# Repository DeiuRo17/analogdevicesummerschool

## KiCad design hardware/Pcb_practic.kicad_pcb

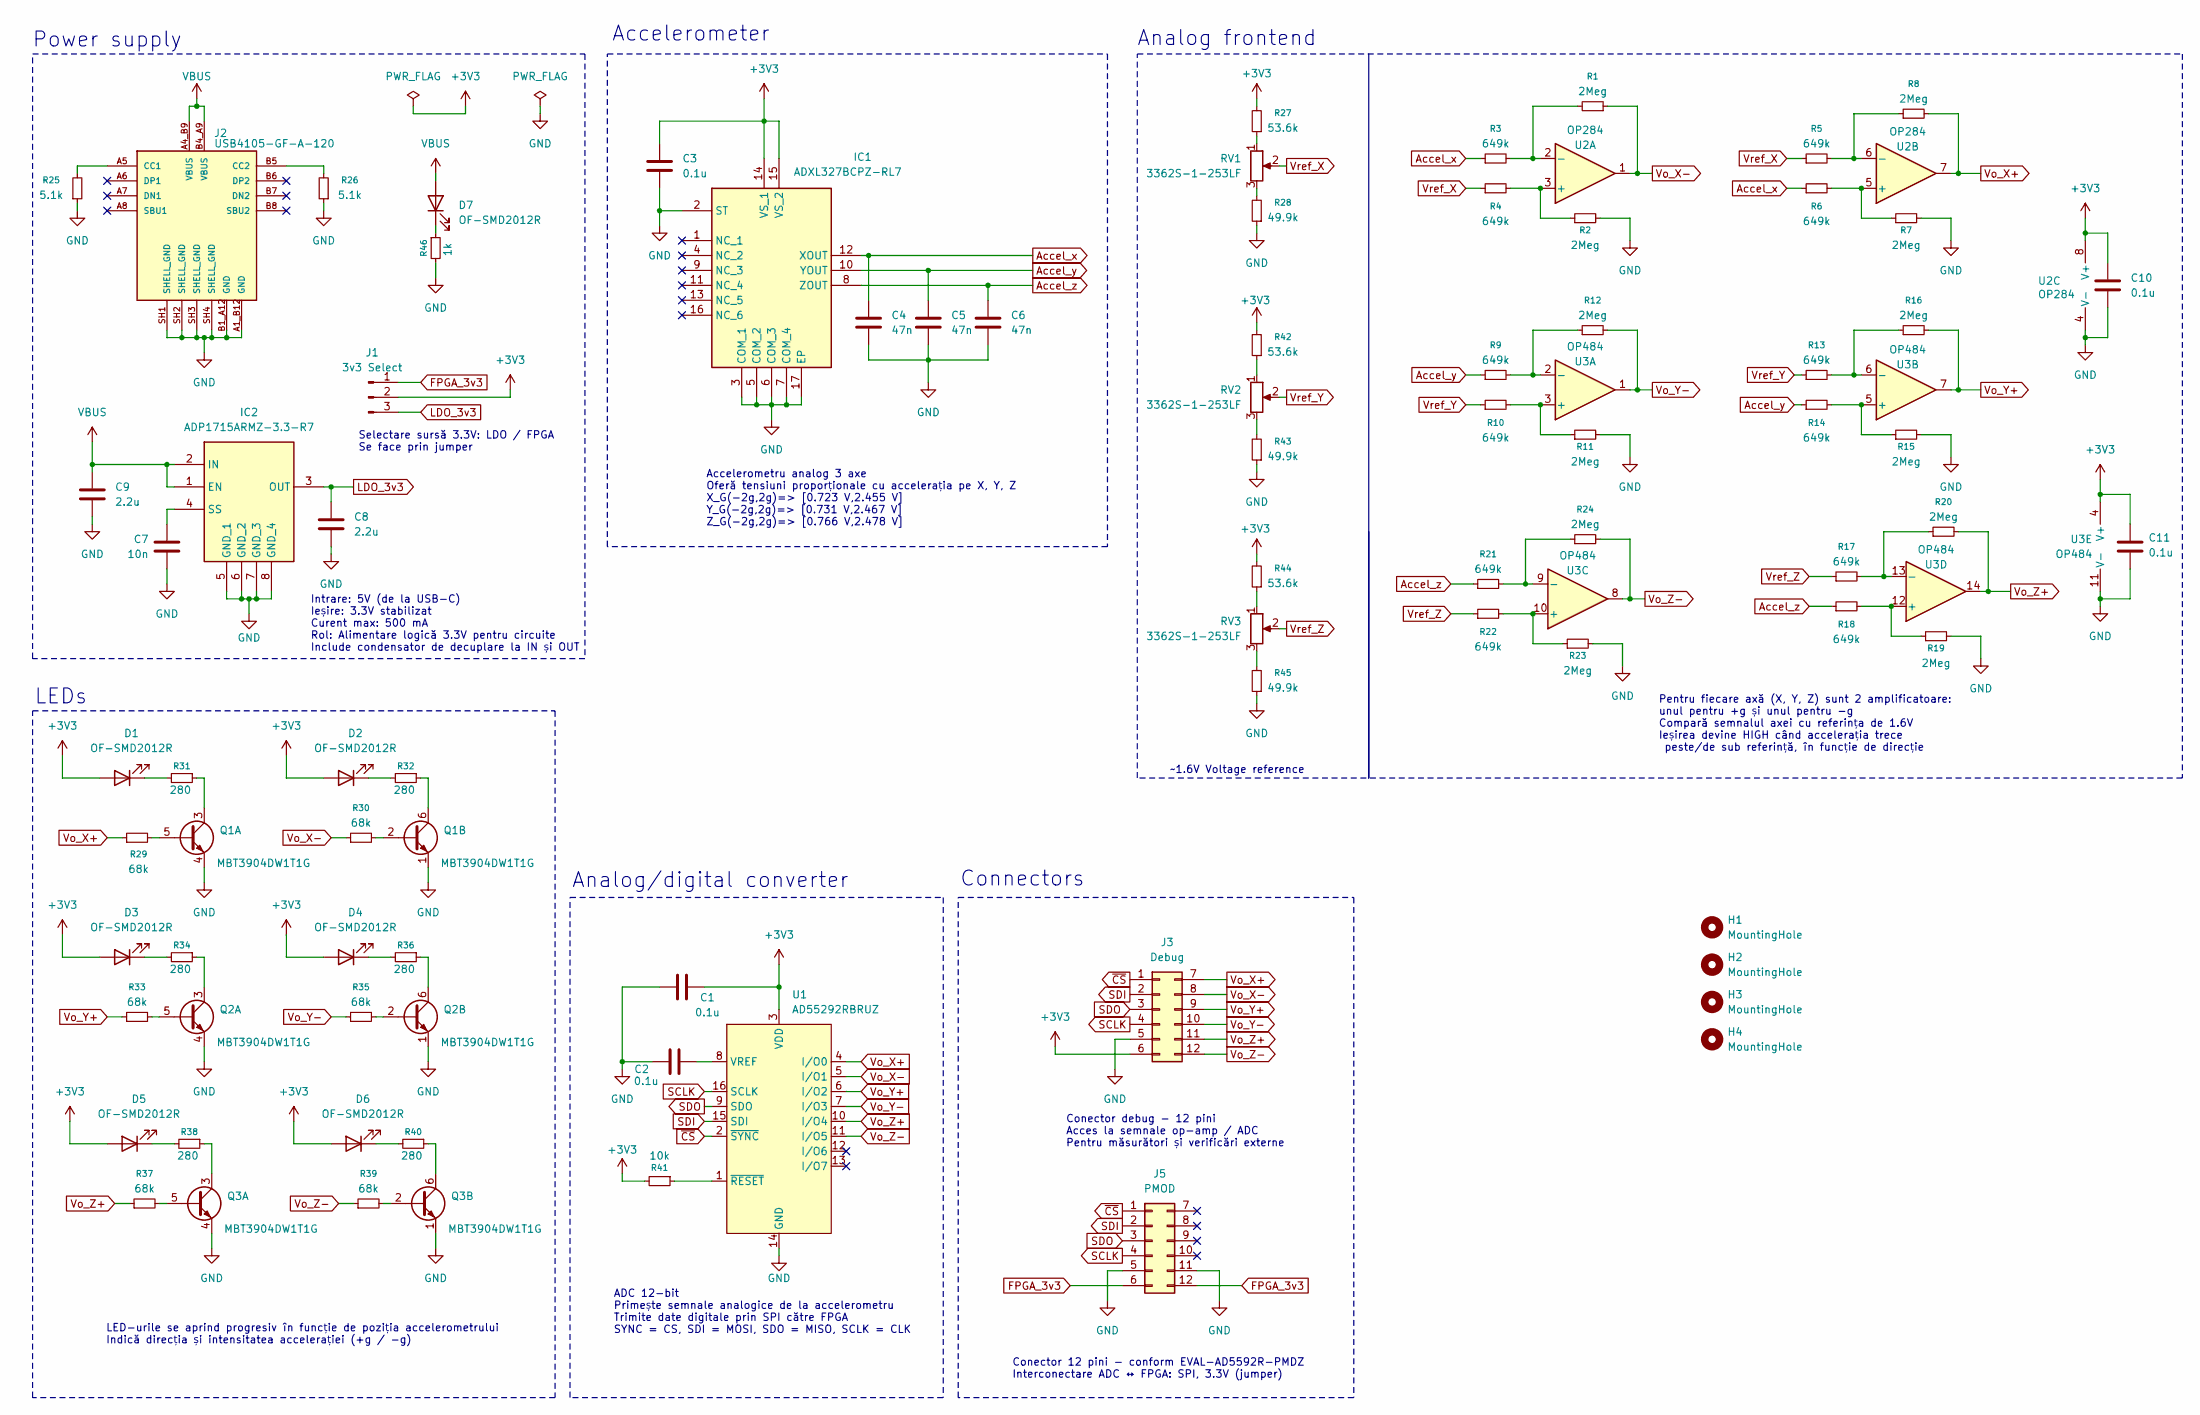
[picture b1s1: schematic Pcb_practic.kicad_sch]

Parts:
C1, C2, C3, C10, C11: 0.1u; C_0603_1608Metric_Pad1.08x0.95mm_HandSolder
C4, C5, C6: 47n; C_0603_1608Metric_Pad1.08x0.95mm_HandSolder
C7: 10n; C_0603_1608Metric_Pad1.08x0.95mm_HandSolder
C8, C9: 2.2u; C_0603_1608Metric_Pad1.08x0.95mm_HandSolder
D1, D2, D3, D4, D5, D6, D7: OF-SMD2012R; LED_0805
H1, H2, H3, H4: MountingHole; MountingHole_2.2mm_M2
IC1: ADXL327BCPZ-RL7; LFCSP_LQ; Manufacturer_Part_Number ADXL327BCPZ-RL7; Mouser Part Number 584-ADXL327BCPZ-R7
IC2: ADP1715ARMZ-3.3-R7; MSOP; Manufacturer_Part_Number ADP1715ARMZ-3.3-R7; Mouser Part Number 584-ADP1715ARMZ3.3R7
J1: 3v3 Select; SAMTEC_TS-103-T-A-1
J2: USB4105-GF-A-120; USB4105-GF-A; PARTREV B3
J3: Debug; 2213S-12G
J5: PMOD; MC34771
Q1, Q2, Q3: MBT3904DW1T1G; SC70−6
R1, R2, R7, R8, R11, R12, R15, R16, R19, R20, R23, R24: 2Meg; R_0603_1608Metric_Pad0.98x0.95mm_HandSolder
R3, R4, R5, R6, R9, R10, R13, R14, R17, R18, R21, R22: 649k; R_0603_1608Metric_Pad0.98x0.95mm_HandSolder
R25, R26: 5.1k; R_0603_1608Metric_Pad0.98x0.95mm_HandSolder
R27, R42, R44: 53.6k; R_0603_1608Metric_Pad0.98x0.95mm_HandSolder
R28, R43, R45: 49.9k; R_0603_1608Metric_Pad0.98x0.95mm_HandSolder
R29, R30, R33, R35, R37, R39: 68k; R_0603_1608Metric_Pad0.98x0.95mm_HandSolder
R31, R32, R34, R36, R38, R40: 280; R_0603_1608Metric_Pad0.98x0.95mm_HandSolder
R41: 10k; R_0603_1608Metric_Pad0.98x0.95mm_HandSolder
R46: 1k; R_0603_1608Metric_Pad0.98x0.95mm_HandSolder
RV1, RV2, RV3: 3362S-1-253LF
U1: AD55292RBRUZ; SOIC-16
U2: OP284; SOIC_N-8
U3: OP484; SOIC_N-14

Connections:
+3V3: C1.2, C3.1, C10.1, C11.1, D1.2 (A), D2.2 (A), D3.2 (A), D4.2 (A), D5.2 (A), D6.2 (A), IC1.14 (VS_1), IC1.15 (VS_2), J1.2, J3.6, R27.2, R41.2, R42.2, R44.2, U1.3 (VDD), U2.8 (V+), U3.4 (V+)
Accel_x: C4.2, IC1.12 (XOUT), R3.1, R6.1
Accel_y: C5.2, IC1.10 (YOUT), R9.1, R14.1
Accel_z: C6.2, IC1.8 (ZOUT), R18.1, R21.1
FPGA_3v3: J1.1, J5.6, J5.12
GND: C1.1, C2.1, C3.2, C4.1, C5.1, C6.1, C7.2, C8.1, C9.1, C10.2, C11.2, IC1.2 (ST), IC1.3 (COM_1), IC1.5 (COM_2), IC1.6 (COM_3), IC1.7 (COM_4), IC1.17 (EP), IC2.5 (GND_1), IC2.6 (GND_2), IC2.7 (GND_3), IC2.8 (GND_4), J2.A1_B12 (GND), J2.B1_A12 (GND), J2.SH1 (SHELL_GND), J2.SH2 (SHELL_GND), J2.SH3 (SHELL_GND), J2.SH4 (SHELL_GND), J3.5, J5.5, J5.11, Q1.1, Q1.4, Q2.1, Q2.4, Q3.1, Q3.4, R2.2, R7.2, R11.2, R15.2, R19.2, R23.2, R25.1, R26.1, R28.1, R43.1, R45.1, R46.2, U1.14 (GND), U2.4 (V-), U3.11 (V-)
LDO_3v3: C8.2, IC2.3 (OUT), J1.3
unnamed: D1.1 (K), R31.2
unnamed: D2.1 (K), R32.2
unnamed: D3.1 (K), R34.2
unnamed: D4.1 (K), R36.2
unnamed: D5.1 (K), R38.2
unnamed: D6.1 (K), R40.2
unnamed: D7.1 (K), R46.1
unnamed: C7.1, IC2.4 (SS)
unnamed: J2.A5 (CC1), R25.2
unnamed: J2.B5 (CC2), R26.2
unnamed: Q1.2, R30.2
unnamed: Q1.3, R31.1
unnamed: Q1.5, R29.2
unnamed: Q1.6, R32.1
unnamed: Q2.2, R35.2
unnamed: Q2.3, R34.1
unnamed: Q2.5, R33.2
unnamed: Q2.6, R36.1
unnamed: Q3.2, R39.2
unnamed: Q3.3, R38.1
unnamed: Q3.5, R37.2
unnamed: Q3.6, R40.1
unnamed: R27.1, RV1.1
unnamed: R28.2, RV1.3
unnamed: R42.1, RV2.1
unnamed: R43.2, RV2.3
unnamed: R44.1, RV3.1
unnamed: R45.2, RV3.3
unnamed: C2.2, U1.8 (VREF)
unnamed: R41.1, U1.1 (~RESET)
unnamed: R2.1, R4.2, U2.3 (+)
unnamed: R6.2, R7.1, U2.5 (+)
unnamed: R5.2, R8.1, U2.6 (-)
unnamed: R10.2, R11.1, U3.3 (+)
unnamed: R9.2, R12.1, U3.2 (-)
unnamed: R14.2, R15.1, U3.5 (+)
unnamed: R13.2, R16.1, U3.6 (-)
unnamed: R22.2, R23.1, U3.10 (+)
unnamed: R21.2, R24.1, U3.9 (-)
unnamed: R18.2, R19.1, U3.12 (+)
unnamed: R17.2, R20.1, U3.13 (-)
SCLK: J3.4, J5.4, U1.16 (SCLK)
SDI: J3.2, J5.2, U1.15 (SDI)
SDO: J3.3, J5.3, U1.9 (SDO)
VBUS: C9.2, D7.2 (A), IC2.1 (EN), IC2.2 (IN), J2.A4_B9 (VBUS), J2.B4_A9 (VBUS)
Vo_X+: J3.7, R8.2, R29.1, U1.4 (I/O0), U2.7
Vo_Y+: J3.9, R16.2, R33.1, U1.6 (I/O2), U3.7
Vo_Y-: J3.10, R12.2, R35.1, U1.7 (I/O3), U3.1
Vo_Z+: J3.11, R20.2, R37.1, U1.10 (I/O4), U3.14
Vo_Z-: J3.12, R24.2, R39.1, U1.11 (I/O5), U3.8
Vref_X: R4.1, R5.1, RV1.2
Vref_Y: R10.1, R13.1, RV2.2
Vref_Z: R17.1, R22.1, RV3.2
~CS: J3.1, J5.1, U1.2 (~SYNC)

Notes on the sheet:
Power supply
Analog frontend
LED-urile se aprind progresiv în funcție de poziția accelerometrului Indică direcția și intensitatea accelerației (+g / -g)
ADC 12-bit Primește semnale analogice de la accelerometru Trimite date digitale prin SPI către FPGA SYNC = CS, SDI = MOSI, SDO = MISO, SCLK = CLK
Intrare: 5V (de la USB-C) Ieșire: 3.3V stabilizat Curent max: 500 mA Rol: Alimentare logică 3.3V pentru circuite Include condensator de decuplare la IN și OUT
Connectors
Analog/digital converter
~1.6V Voltage reference
LEDs
Accelerometru analog 3 axe Oferă tensiuni proporționale cu accelerația pe X, Y, Z X_G(-2g,2g)=> [0.723 V,2.455 V] Y_G(-2g,2g)=> [0.731 V,2.467 V] Z_G(-2g,2g)=> [0.766 V,2.478 V]
Accelerometer
Pentru fiecare axă (X, Y, Z) sunt 2 amplificatoare: unul pentru +g și unul pentru -g Compară semnalul axei cu referința de 1.6V Ieșirea devine HIGH când accelerația trece peste/de sub referință, în funcție de direcție
Conector debug - 12 pini Acces la semnale op-amp / ADC Pentru măsurători și verificări externe
Selectare sursă 3.3V: LDO / FPGA Se face prin jumper
Conector 12 pini - conform EVAL-AD5592R-PMDZ Interconectare ADC ↔ FPGA: SPI, 3.3V (jumper)

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
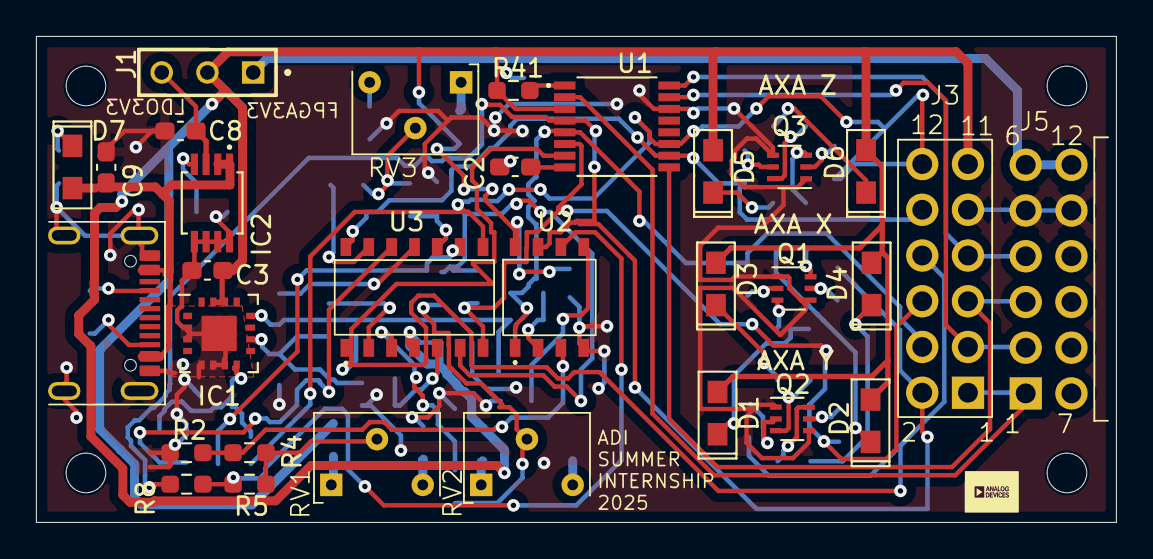
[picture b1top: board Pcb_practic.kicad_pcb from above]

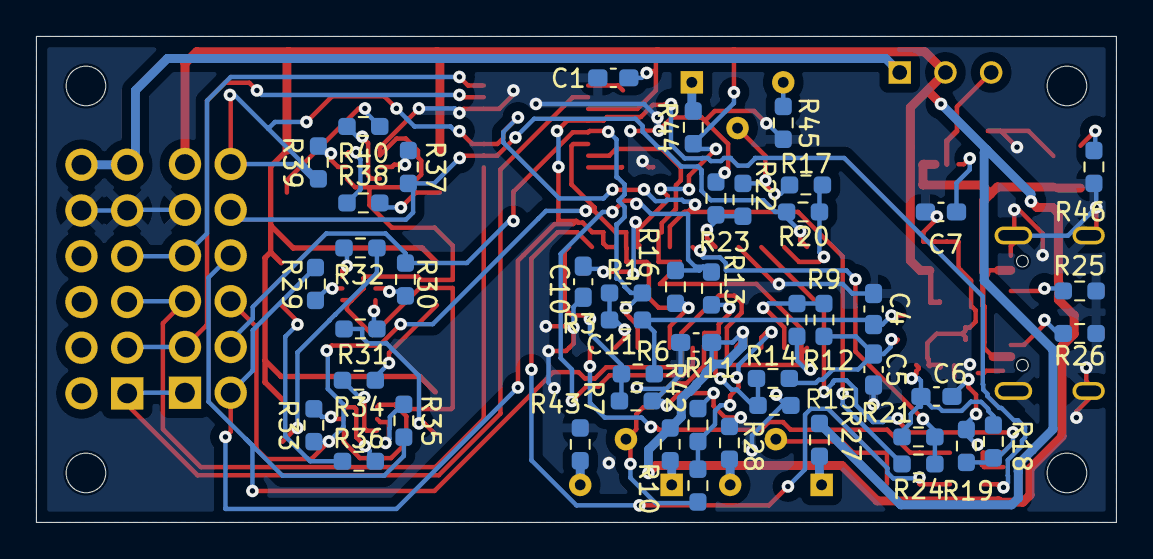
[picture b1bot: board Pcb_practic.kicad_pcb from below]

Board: 2 copper layers, 60.0 x 27.0 mm, 83 parts (48 on the bottom side), 63 nets.

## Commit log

2025-09-25 Adăugat folderul axi_pwm_custom din ADI Summer School
2025-09-25 Driver for the adc
2025-09-25 Adăugat folderul iio-apps-2025
2025-09-25 Adăugat iio-apps-2025 corect în folder nou
2025-09-25 Adăugat folderul hardware cu fișierele din Andrei_Bota_2025
2025-09-25 Redenumit iio-apps-2025-new în iio_apps
2025-09-25 Redenumit iio_pwm_custom in HDL
2025-10-02 Removed iio-apps-2025 folder
2025-10-02 -Created a new folder for embedded soft
2025-10-02 Removed the embedded soft code
